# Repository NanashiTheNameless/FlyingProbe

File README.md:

# FlyingProbe

"FlyingProbe" is a personal project of mine designed to replicate those cool SD Card Debuggers.

## Hardware Notes

Inside [The hardware folder](<https://github.com/NanashiTheNameless/FlyingProbe/tree/main/Hardware>) is a large set of renders to describe a design for a probe.

The small (yellow) spring can be a pen spring or something similar.

The probe rod (orange) can be a bent accupuncture needle or paperclip of some kind.

You can also theoretically use a premade probe like this one from [AliExpress](<https://www.aliexpress.com/item/3256803993646501.html>).
Although I make no promises of it truly working, it _should_ work, so use at your own risk.

**!!! A Washer should be added in between the bottom spring and the PCB !!!**

## Production

Gerber files can be found [here](<https://github.com/NanashiTheNameless/FlyingProbe/raw/refs/heads/main/production/FlyingProbe.zip>).

## License

This project licensed under OQL [found here](<license.md>).

## Extra Considerations

The following files are not mine and are referenced from [McMaster-Carr](<https://www.mcmaster.com>) all credit for and ownership of the files is solely theirs and I take no credit for them and claim no ownership of them, <ins>**as such my license _does not_ apply to them**</ins>:

[Hardware/8969T477_316 Stainless Steel Corrosion-Resistant Compression Springs.PDF](<Hardware/8969T477_316 Stainless Steel Corrosion-Resistant Compression Springs.PDF>)

[Hardware/92319A294_Nylon 6-6 Plastic Hex Standoff.PDF](<Hardware/92319A294_Nylon 6-6 Plastic Hex Standoff.PDF>)

[Hardware/92319A296_Nylon 6-6 Plastic Hex Standoff.PDF](<Hardware/92319A296_Nylon 6-6 Plastic Hex Standoff.PDF>)

[Hardware/92319A307_Nylon 6-6 Plastic Hex Standoff.PDF](<Hardware/92319A307_Nylon 6-6 Plastic Hex Standoff.PDF>)

[Hardware/92625A106_Stainless Steel Wing-Head Thumb Screw.PDF](<Hardware/92625A106_Stainless Steel Wing-Head Thumb Screw.PDF>)

[Hardware/94792A114_316 Stainless Steel Extra-Wide Truss Head Phillips Screws.PDF](<Hardware/94792A114_316 Stainless Steel Extra-Wide Truss Head Phillips Screws.PDF>)

[Hardware/94868A011_Female Threaded Hex Standoff.PDF](<Hardware/94868A011_Female Threaded Hex Standoff.PDF>)

[Hardware/96367A935_High-Strength High-Temperature PEEK Screw.PDF](<Hardware/96367A935_High-Strength High-Temperature PEEK Screw.PDF>)

###### Note to [McMaster-Carr](<https://www.mcmaster.com>), If this is not your intended meaning of "reference use", Please open a github issue/PR and I'll do my best to reach an acceptable solution.

###### Please do not use these PDF files to manufacture any of the parts they describe, Using someone else's designs without paying for them or being explicitly allowed to is a scummy thing to do, please just buy the parts instead of reproducing them without permission, or just make your own completely new custom parts.

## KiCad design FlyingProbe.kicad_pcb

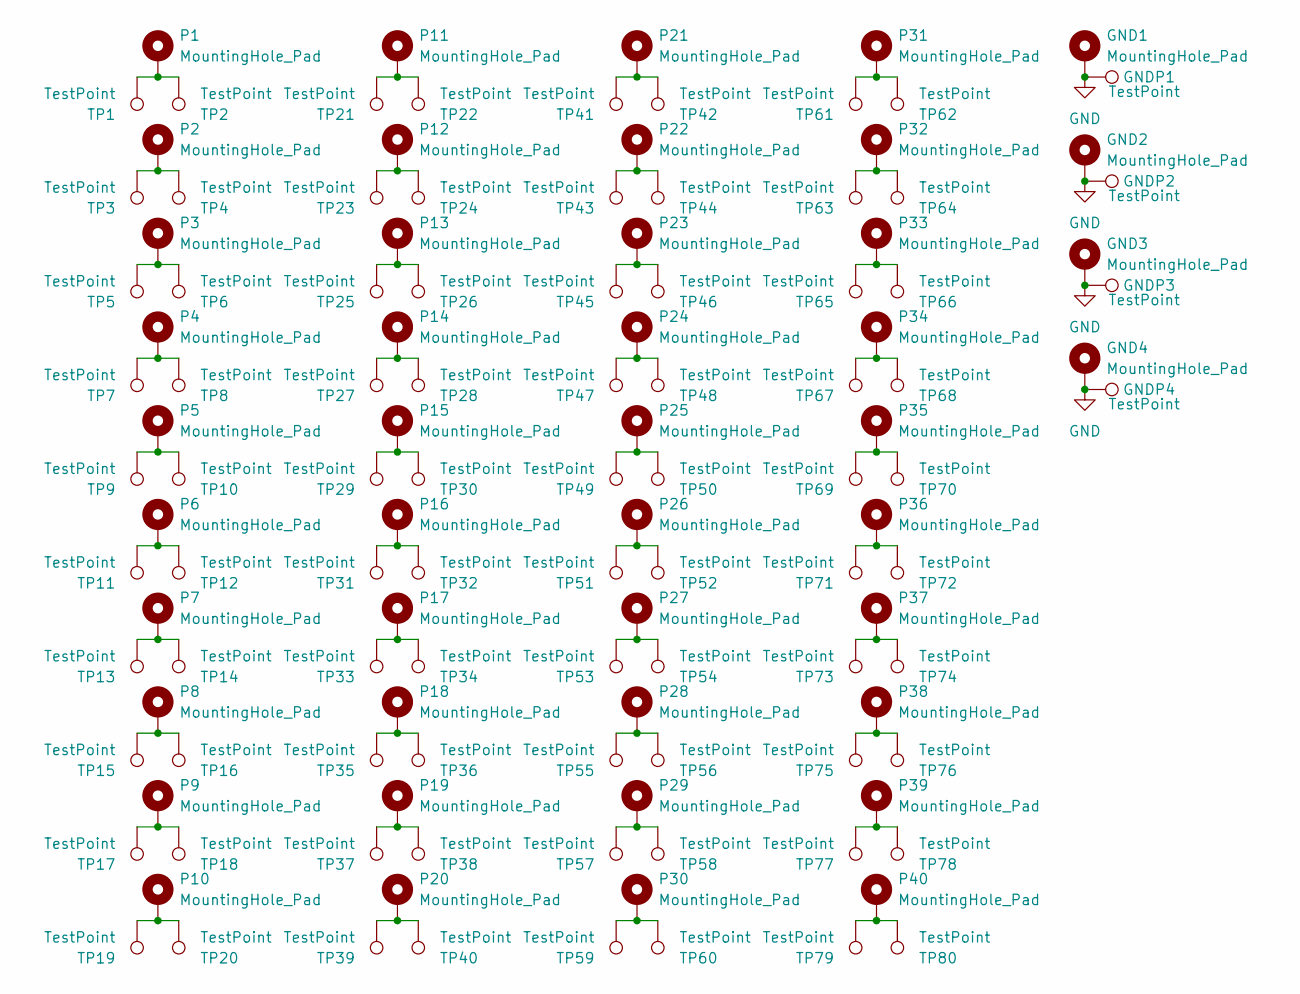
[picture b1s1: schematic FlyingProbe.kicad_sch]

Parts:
GND1, GND2, GND3, GND4: MountingHole_Pad; MountingHole_3.2mm_M3_Pad_Via
GNDP1, GNDP2, GNDP3, GNDP4: TestPoint; Pin_D1.0mm_L10.0mm_LooseFit
P1, P2, P3, P4, P5, P6, P7, P8, P9, P10, P11, P12, P13, P14, P15, P16, P17, P18, P19, P20, P21, P22, P23, P24, P25, P26, P27, P28, P29, P30, P31, P32, P33, P34, P35, P36, P37, P38, P39, P40: MountingHole_Pad; MountingHole_3.2mm_M3_Pad_Via
TP1, TP2, TP3, TP4, TP5, TP6, TP7, TP8, TP9, TP10, TP11, TP12, TP13, TP14, TP15, TP16, TP17, TP18, TP19, TP20, TP21, TP22, TP23, TP24, TP25, TP26, TP27, TP28, TP29, TP30, TP31, TP32, TP33, TP34, TP35, TP36, TP37, TP38, TP39, TP40, TP41, TP42, TP43, TP44, TP45, TP46, TP47, TP48, TP49, TP50, TP51, TP52, TP53, TP54, TP55, TP56, TP57, TP58, TP59, TP60, TP61, TP62, TP63, TP64, TP65, TP66, TP67, TP68, TP69, TP70, TP71, TP72, TP73, TP74, TP75, TP76, TP77, TP78, TP79, TP80: TestPoint; Pin_D1.0mm_L10.0mm_LooseFit

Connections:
GND: GND1.1, GND2.1, GND3.1, GND4.1, GNDP1.1, GNDP2.1, GNDP3.1, GNDP4.1
unnamed: P1.1, TP1.1, TP2.1
unnamed: P2.1, TP3.1, TP4.1
unnamed: P3.1, TP5.1, TP6.1
unnamed: P4.1, TP7.1, TP8.1
unnamed: P5.1, TP9.1, TP10.1
unnamed: P6.1, TP11.1, TP12.1
unnamed: P7.1, TP13.1, TP14.1
unnamed: P8.1, TP15.1, TP16.1
unnamed: P9.1, TP17.1, TP18.1
unnamed: P10.1, TP19.1, TP20.1
unnamed: P11.1, TP21.1, TP22.1
unnamed: P12.1, TP23.1, TP24.1
unnamed: P13.1, TP25.1, TP26.1
unnamed: P14.1, TP27.1, TP28.1
unnamed: P15.1, TP29.1, TP30.1
unnamed: P16.1, TP31.1, TP32.1
unnamed: P17.1, TP33.1, TP34.1
unnamed: P18.1, TP35.1, TP36.1
unnamed: P19.1, TP37.1, TP38.1
unnamed: P20.1, TP39.1, TP40.1
unnamed: P21.1, TP41.1, TP42.1
unnamed: P22.1, TP43.1, TP44.1
unnamed: P23.1, TP45.1, TP46.1
unnamed: P24.1, TP47.1, TP48.1
unnamed: P25.1, TP49.1, TP50.1
unnamed: P26.1, TP51.1, TP52.1
unnamed: P27.1, TP53.1, TP54.1
unnamed: P28.1, TP55.1, TP56.1
unnamed: P29.1, TP57.1, TP58.1
unnamed: P30.1, TP59.1, TP60.1
unnamed: P31.1, TP61.1, TP62.1
unnamed: P32.1, TP63.1, TP64.1
unnamed: P33.1, TP65.1, TP66.1
unnamed: P34.1, TP67.1, TP68.1
unnamed: P35.1, TP69.1, TP70.1
unnamed: P36.1, TP71.1, TP72.1
unnamed: P37.1, TP73.1, TP74.1
unnamed: P38.1, TP75.1, TP76.1
unnamed: P39.1, TP77.1, TP78.1
unnamed: P40.1, TP79.1, TP80.1

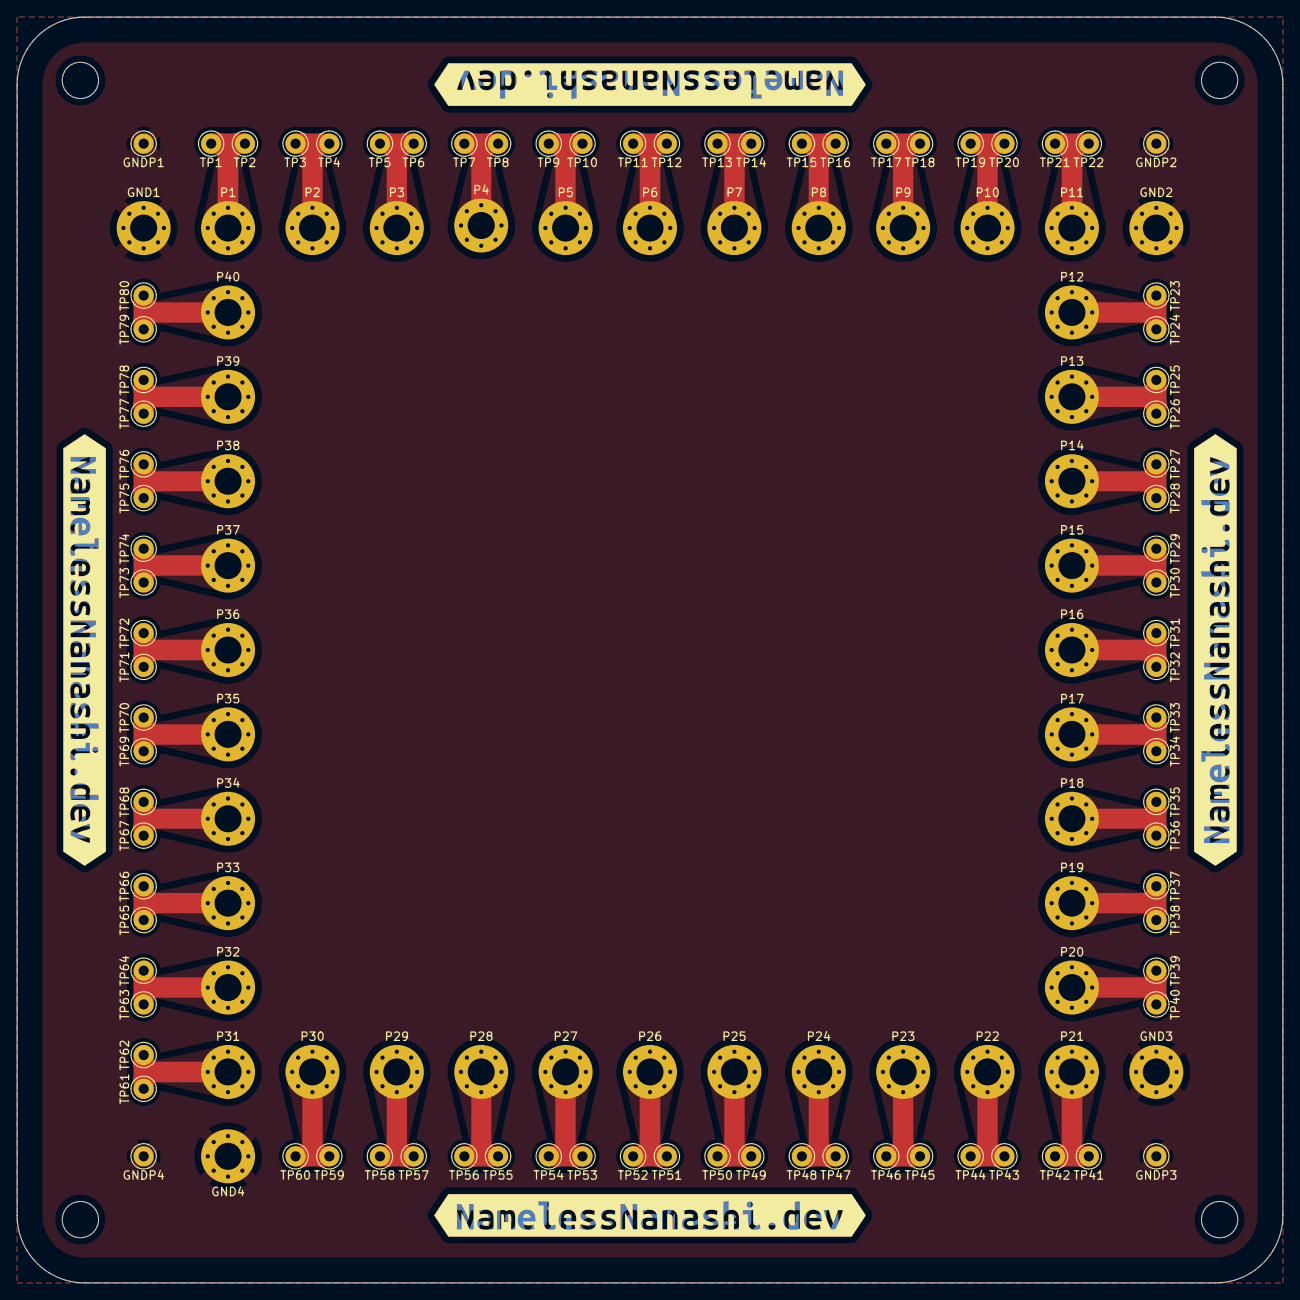
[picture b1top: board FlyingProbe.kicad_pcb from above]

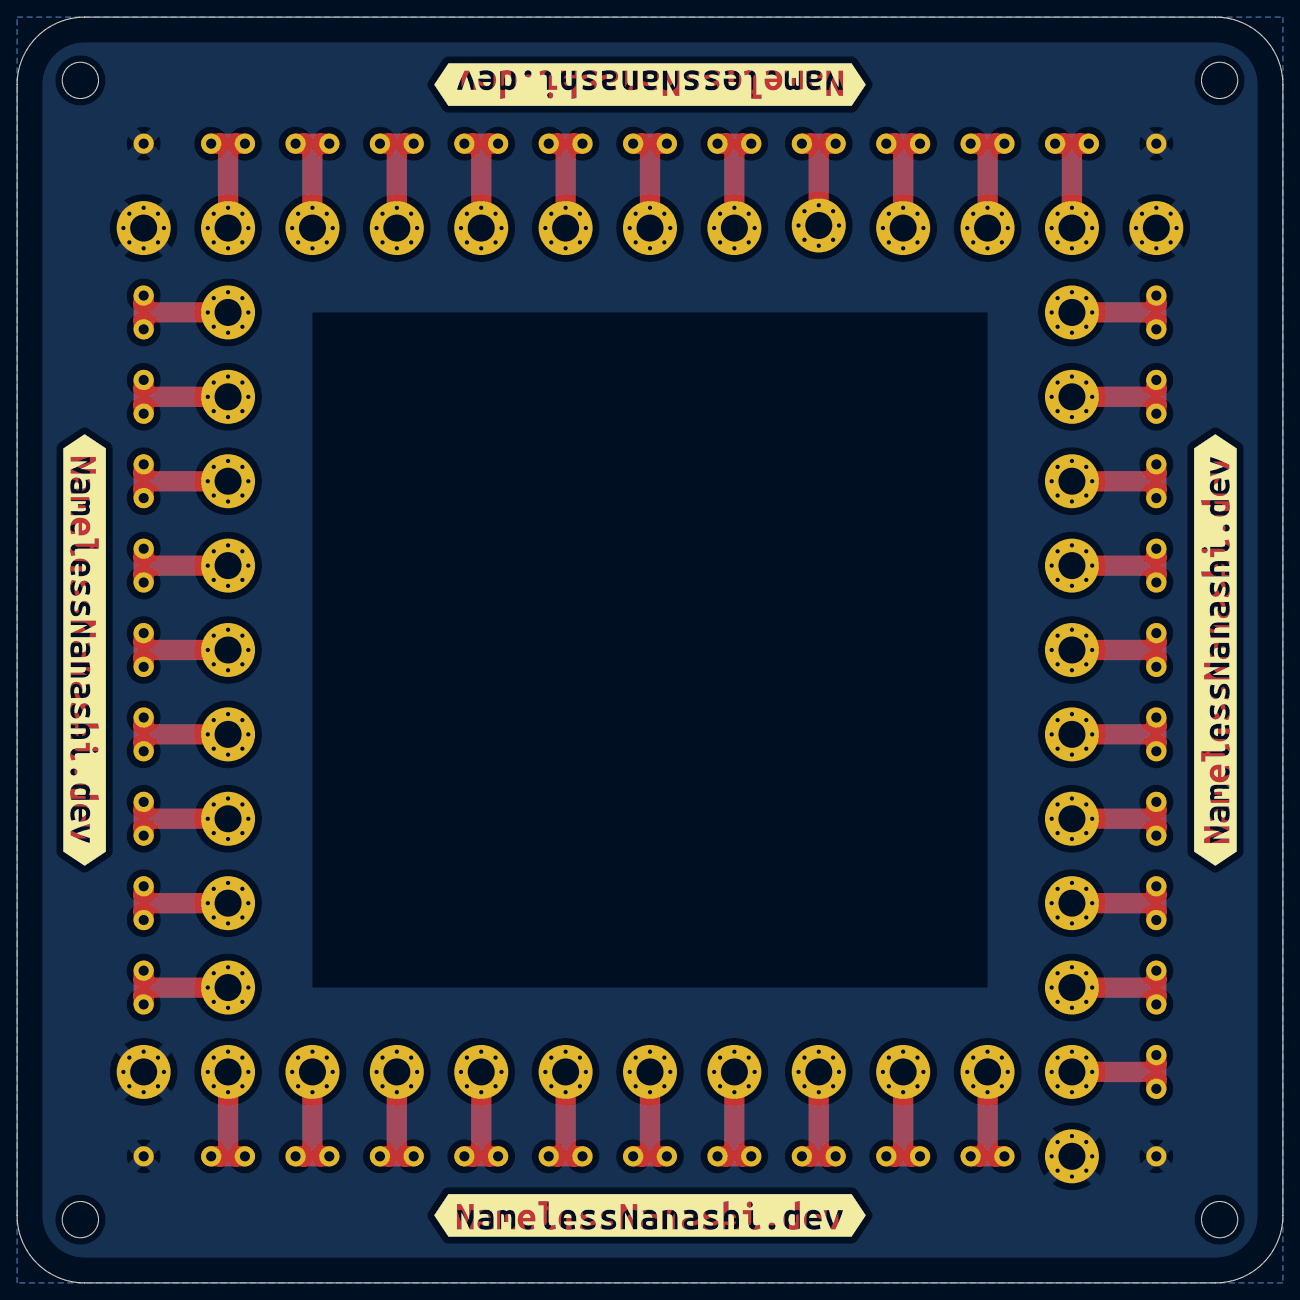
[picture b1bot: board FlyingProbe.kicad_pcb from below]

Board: 2 copper layers, 150.0 x 150.0 mm, 148 parts (8 on the bottom side), 41 nets.

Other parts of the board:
MH1, MH2, MH3, MH4: MountingHole_4.3mm_M4
kibuzzard-6757E0AC, kibuzzard-6757E0AC#2, kibuzzard-6757E0AC#3, kibuzzard-6757E0AC#4: G***; kibuzzard-6757E0AC
kibuzzard-6757E0B3, kibuzzard-6757E0B3#2, kibuzzard-6757E0B3#3, kibuzzard-6757E0B3#4: G***; kibuzzard-6757E0B3
kibuzzard-6757E0BA, kibuzzard-6757E0BA#2, kibuzzard-6757E0BA#3, kibuzzard-6757E0BA#4: G***; kibuzzard-6757E0BA
kibuzzard-6757E0C1, kibuzzard-6757E0C1#2, kibuzzard-6757E0C1#3, kibuzzard-6757E0C1#4: G***; kibuzzard-6757E0C1

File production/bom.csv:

Designator,Footprint,Quantity,Value,LCSC Part #
"GNDP1, GNDP2, GNDP3, GNDP4, TP1, TP10, TP11, TP12, TP13, TP14, TP15, TP16, TP17, TP18, TP19, TP2, TP20, TP21, TP22, TP23, TP24, TP25, TP26, TP27, TP28, TP29, TP3, TP30, TP31, TP32, TP33, TP34, TP35, TP36, TP37, TP38, TP39, TP4, TP40, TP41, TP42, TP43, TP44, TP45, TP46, TP47, TP48, TP49, TP5, TP50, TP51, TP52, TP53, TP54, TP55, TP56, TP57, TP58, TP59, TP6, TP60, TP61, TP62, TP63, TP64, TP65, TP66, TP67, TP68, TP69, TP7, TP70, TP71, TP72, TP73, TP74, TP75, TP76, TP77, TP78, TP79, TP8, TP80, TP9",Pin_D1.0mm_L10.0mm_LooseFit,84,TestPoint,

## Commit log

2024-12-11 Add initial version
2024-12-11 Update README.md
    Update Gerber link to be a download
2024-12-11 Update README.md
    Update the link to the hardware folder
2024-12-11 add a disclaimer
2024-12-12 Update README.md to update formatting
